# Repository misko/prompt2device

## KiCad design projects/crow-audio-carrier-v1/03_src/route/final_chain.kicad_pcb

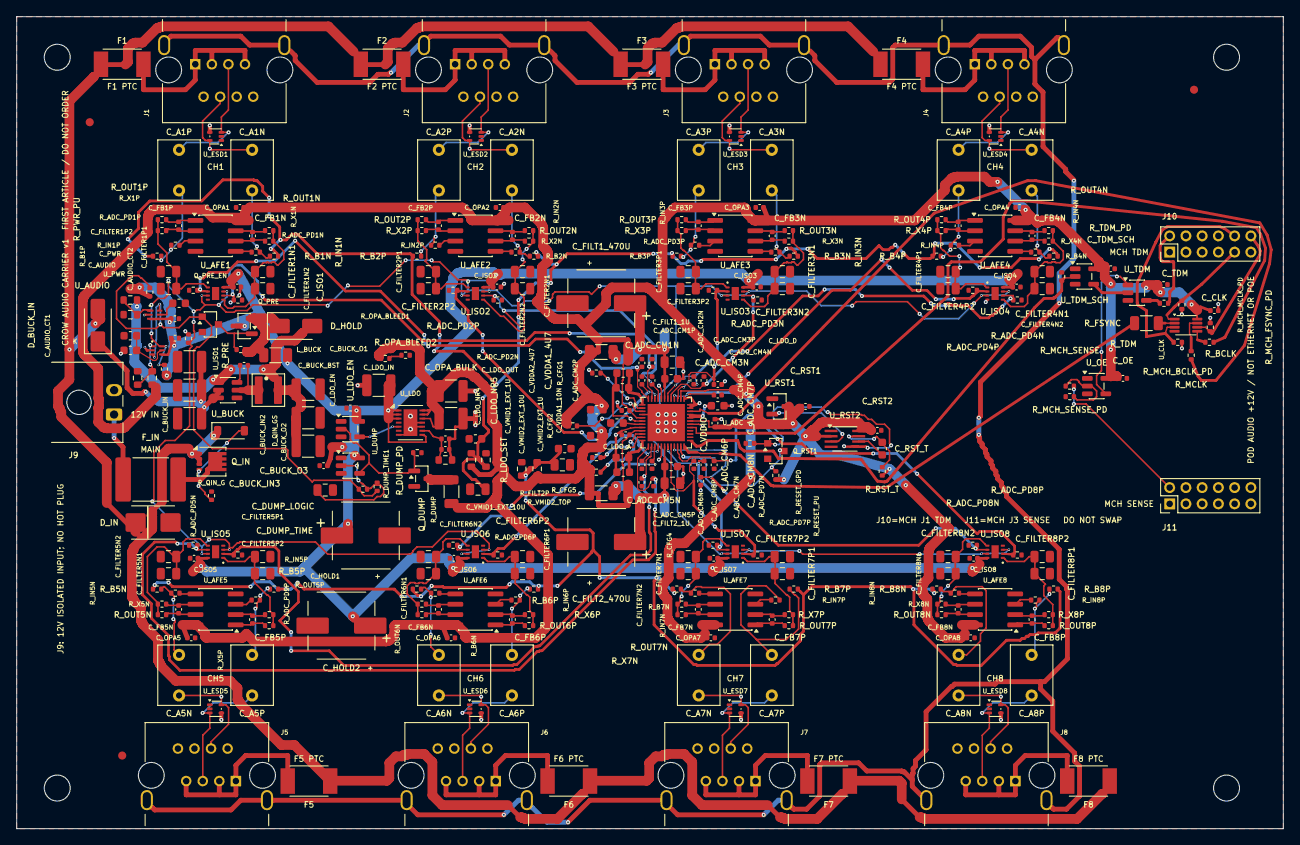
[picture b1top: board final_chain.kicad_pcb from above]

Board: 4 copper layers, 156.0 x 100.0 mm, 340 parts (0 on the bottom side), 179 nets.

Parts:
C_A1N, C_A1P, C_A2N, C_A2P, C_A3N, C_A3P, C_A4N, C_A4P, C_A5N, C_A5P, C_A6N, C_A6P, C_A7N, C_A7P, C_A8N, C_A8P: 1uF; C_Rect_L7.2mm_W5.0mm_P5.00mm
C_ADC_CM1N, C_ADC_CM1P, C_ADC_CM2N, C_ADC_CM2P, C_ADC_CM3N, C_ADC_CM3P, C_ADC_CM4N, C_ADC_CM4P, C_ADC_CM5N, C_ADC_CM5P, C_ADC_CM6N, C_ADC_CM6P, C_ADC_CM7N, C_ADC_CM7P, C_ADC_CM8N, C_ADC_CM8P: 1nF; C_0402_1005Metric
C_AUDIO: 100nF; C_0402_1005Metric
C_AUDIO_CT1, C_AUDIO_CT2: 1uF; C_0603_1608Metric
C_BUCK_BST: 100nF; C_0402_1005Metric
C_BUCK_IN, C_BUCK_IN2, C_BUCK_IN3: 10uF; C_1210_3225Metric
C_BUCK_O1, C_BUCK_O2, C_BUCK_O3: 47uF; C_1210_3225Metric
C_CLK: 100nF; C_0402_1005Metric
C_DUMP_LOGIC: 100nF; C_0402_1005Metric
C_DUMP_TIME: 15nF; C_0805_2012Metric
C_FB1N, C_FB1P, C_FB2N, C_FB2P, C_FB3N, C_FB3P, C_FB4N, C_FB4P, C_FB5N, C_FB5P, C_FB6N, C_FB6P, C_FB7N, C_FB7P, C_FB8N, C_FB8P: 680pF; C_0402_1005Metric
C_FILT1_1U, C_FILT2_1U: 1uF; C_0603_1608Metric
C_FILT1_10U, C_FILT2_10U: 10uF; C_0805_2012Metric
C_FILT1_470U, C_FILT2_470U: 470uF; Panasonic_EEEFK1A471P_8x10.2_Exact
C_FILTER1N1, C_FILTER1N2, C_FILTER1P1, C_FILTER1P2, C_FILTER2N1, C_FILTER2N2, C_FILTER2P1, C_FILTER2P2, C_FILTER3N1, C_FILTER3N2, C_FILTER3P1, C_FILTER3P2, C_FILTER4N1, C_FILTER4N2, C_FILTER4P1, C_FILTER4P2, C_FILTER5N1, C_FILTER5N2, C_FILTER5P1, C_FILTER5P2, C_FILTER6N1, C_FILTER6N2, C_FILTER6P1, C_FILTER6P2, C_FILTER7N1, C_FILTER7N2, C_FILTER7P1, C_FILTER7P2, C_FILTER8N1, C_FILTER8N2, C_FILTER8P1, C_FILTER8P2: 15nF; C_0805_2012Metric
C_HOLD1, C_HOLD2: 470uF; Panasonic_EEEFK1A471P_8x10.2_Exact
C_ISO1, C_ISO2, C_ISO3, C_ISO4, C_ISO5, C_ISO6, C_ISO7, C_ISO8: 100nF; C_0402_1005Metric
C_LDO_A: 4.7uF; C_0603_1608Metric
C_LDO_D: 4.7uF; C_0603_1608Metric
C_LDO_EN: 100nF; C_0402_1005Metric
C_LDO_IN: 47uF; C_1210_3225Metric
C_LDO_NR4, C_LDO_NR5: 1nF; C_0402_1005Metric
C_LDO_OUT: 47uF; C_1210_3225Metric
C_OE: 100nF; C_0402_1005Metric
C_OPA1, C_OPA2, C_OPA3, C_OPA4, C_OPA5, C_OPA6, C_OPA7, C_OPA8: 100nF; C_0402_1005Metric
C_OPA_BULK: 47uF; C_1210_3225Metric
C_PWR: 100nF; C_0402_1005Metric
C_PWR_CT: 1uF; C_0603_1608Metric
C_RST1, C_RST2: 100nF; C_0402_1005Metric
C_RST_T: 220nF; C_0603_1608Metric
C_TDM: 100nF; C_0402_1005Metric
C_TDM_SCH: 100nF; C_0402_1005Metric
C_VDDA1_4U7, C_VDDA2_4U7: 4.7uF; C_0603_1608Metric
C_VDDA1_10N, C_VDDA2_10N: 10nF; C_0402_1005Metric
C_VDDIO: 100nF; C_0402_1005Metric
C_VMID1_4U7, C_VMID2_4U7: 4.7uF; C_0603_1608Metric
C_VMID1_470N, C_VMID2_470N: 470nF; C_0603_1608Metric
C_VMID1_EXT_1U, C_VMID2_EXT_1U: 1uF; C_0603_1608Metric
C_VMID1_EXT_10U, C_VMID2_EXT_10U: 10uF; C_0805_2012Metric
D_BUCK_IN: US1B-13-F; D_SMA
D_HOLD: B340A-13-F; D_SMA
D_IN: SMBJ15A; Littelfuse_SMBJ15A_SMB_Exact
D_QIN_GS: BZT52C12-7-F; D_SOD-123
F1, F2, F3, F4, F5, F6, F7, F8: 1812L035/60MR; Littelfuse_1812L035_60_Exact
FID1, FID2, FID3: Fiducial_1mm_Mask2mm
F_IN: 2920L260/33DR; Fuse_2920_7451Metric
H1, H2, H3, H4: MountingHole_3.2mm_M3
J1, J2, J3, J4, J5, J6, J7, J8: 615008160221; Wurth_615008160221_RJ45
J9: 43650-0200; Molex_43650-0200_RA_Exact
J10, J11: TMM-106-01-L-D; Samtec_TMM-106-01-L-D_2x06_P2.00mm_Vertical
L_BUCK: XGL4020-332MEC; Coilcraft_XGL4020_Exact
Q_DUMP: AO3400A; SOT-23
Q_IN: DMP6023LFG-13; Diodes_PowerDI3333-8
Q_PRE: AO3401A; SOT-23
Q_PRE_EN: 2N7002K-7; Diodes_2N7002K_SOT23_Exact
Q_RST1: 2N7002K-7; Diodes_2N7002K_SOT23_Exact
R_ADC_BOT: 10kΩ; R_0603_1608Metric
R_ADC_PD1N, R_ADC_PD1P, R_ADC_PD2N, R_ADC_PD2P, R_ADC_PD3N, R_ADC_PD3P, R_ADC_PD4N, R_ADC_PD4P, R_ADC_PD5N, R_ADC_PD5P, R_ADC_PD6N, R_ADC_PD6P, R_ADC_PD7N, R_ADC_PD7P, R_ADC_PD8N, R_ADC_PD8P: 10kΩ; R_0402_1005Metric
R_ADC_TOP: 17.4kΩ; R_0603_1608Metric
R_AUDIO_PD: 100kΩ; R_0402_1005Metric
R_AUDIO_PU: 10kΩ; R_0402_1005Metric
R_B1N, R_B1P, R_B2N, R_B2P, R_B3N, R_B3P, R_B4N, R_B4P, R_B5N, R_B5P, R_B6N, R_B6P, R_B7N, R_B7P, R_B8N, R_B8P: 100kΩ; R_0402_1005Metric
R_BCLK: 22Ω; R_0402_1005Metric
R_CFG1, R_CFG4: 4.7kΩ; R_0402_1005Metric
R_CFG2: 0Ω; R_0402_1005Metric
R_CFG5: 100kΩ; R_0402_1005Metric
R_DUMP: 1Ω; R_1206_3216Metric
R_DUMP_PD: 100kΩ; R_0402_1005Metric
R_DUMP_TIME1, R_DUMP_TIME2: 100kΩ; R_0402_1005Metric
R_FILT1P, R_FILT2P: 1Ω; R_1206_3216Metric
R_FSYNC: 22Ω; R_1206_3216Metric
R_IN1N, R_IN1P, R_IN2N, R_IN2P, R_IN3N, R_IN3P, R_IN4N, R_IN4P, R_IN5N, R_IN5P, R_IN6N, R_IN6P, R_IN7N, R_IN7P, R_IN8N, R_IN8P: 10kΩ; R_0402_1005Metric
R_LDO_SET: 33kΩ; R_0603_1608Metric
R_MCH_BCLK_PD: 10kΩ; R_0402_1005Metric
R_MCH_FSYNC_PD: 10kΩ; R_0402_1005Metric
R_MCH_MCLK_PD: 10kΩ; R_0402_1005Metric
R_MCH_SENSE: 300Ω; R_0402_1005Metric
R_MCH_SENSE_PD: 10kΩ; R_0402_1005Metric
R_MCLK: 22Ω; R_0402_1005Metric
R_OPA_BLEED1, R_OPA_BLEED2: 100Ω; R_0402_1005Metric
R_OUT1N, R_OUT1P, R_OUT2N, R_OUT2P, R_OUT3N, R_OUT3P, R_OUT4N, R_OUT4P, R_OUT5N, R_OUT5P, R_OUT6N, R_OUT6P, R_OUT7N, R_OUT7P, R_OUT8N, R_OUT8P: 10Ω; R_0402_1005Metric
R_PRE: 22Ω; R_1206_3216Metric
R_PRE_G: 100kΩ; R_0402_1005Metric
R_PWR_BOT: 10kΩ; R_0603_1608Metric
R_PWR_PU: 10kΩ; R_0402_1005Metric
R_PWR_TOP: 30.9kΩ; Yageo_RT0603_NominalBody
R_QIN_G: 100kΩ; R_0402_1005Metric
R_RESET_GPD: 100kΩ; R_0402_1005Metric
R_RESET_PU: 10kΩ; R_0402_1005Metric
R_RST_T: 100kΩ; R_0402_1005Metric
R_TDM: 33Ω; R_0402_1005Metric
R_TDM_PD: 10kΩ; R_0402_1005Metric
R_VMID1_BOT, R_VMID1_TOP, R_VMID2_BOT, R_VMID2_TOP: 1kΩ; R_0603_1608Metric
R_X1N, R_X1P, R_X2N, R_X2P, R_X3N, R_X3P, R_X4N, R_X4P, R_X5N, R_X5P, R_X6N, R_X6P, R_X7N, R_X7P, R_X8N, R_X8P: 300Ω; R_0402_1005Metric
U_ADC: CS5308P-DN; Cirrus_CS5308P_QFN48_6x6_P0.4_EP4.6
U_AFE1, U_AFE2, U_AFE3, U_AFE4, U_AFE5, U_AFE6, U_AFE7, U_AFE8: OPA2320AIDR; SOIC-8_3.9x4.9mm_P1.27mm
U_AUDIO: TPS389001DSER; TI_DSE0006A_GNDToe018
U_BUCK: AP63205WU-7; TSOT-23-6
U_CLK: SN74LVC3G34DCUR; VSSOP-8_2.3x2mm_P0.5mm
U_DUMP: 74LVC1G14GV,125; SOT-23-5
U_ESD1, U_ESD2, U_ESD3, U_ESD4, U_ESD5, U_ESD6, U_ESD7, U_ESD8: TPD2E2U06DRLR; SOT-553
U_ISO1, U_ISO2, U_ISO3, U_ISO4, U_ISO5, U_ISO6, U_ISO7, U_ISO8: TMUX2821DSGR; TI_DSG0008A_Exact
U_LDO: LT3041ADE#TRPBF; DFN-14-1EP_3x4mm_P0.5mm_EP1.7x3.3mm
U_LDO_EN: 74LVC1G14GV,125; SOT-23-5
U_OE: 74LVC1G14GV,125; SOT-23-5
U_PWR: TPS389001DSER; TI_DSE0006A_GNDToe018
U_RST1: TPS3839K33DBZR; SOT-23
U_RST2: SN74LVC1G123DCTR; SSOP-8_2.95x2.8mm_P0.65mm
U_TDM: SN74LVC1G125DBVR; SOT-23-5
U_TDM_SCH: 74LVC1G17GV,125; SOT-23-5

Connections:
3V3_ADC: C_CLK.1, C_LDO_OUT.1, C_OE.1, C_OPA1.1, C_OPA2.1, C_OPA3.1, C_OPA4.1, C_OPA5.1, C_OPA6.1, C_OPA7.1, C_OPA8.1, C_OPA_BULK.1, C_RST1.1, C_RST2.1, C_TDM.1, C_TDM_SCH.1, C_VDDA1_4U7.1, C_VDDA1_10N.1, C_VDDA2_4U7.1, C_VDDA2_10N.1, C_VDDIO.1, R_ADC_TOP.1, R_CFG2.2, R_CFG4.2, R_DUMP.1, R_FILT1P.1, R_FILT2P.1, R_OPA_BLEED1.1, R_RESET_PU.1, R_RST_T.1, R_VMID1_TOP.1, R_VMID2_TOP.1, U_ADC.5, U_ADC.9, U_ADC.31, U_ADC.38, U_AFE1.8, U_AFE2.8, U_AFE3.8, U_AFE4.8, U_AFE5.8, U_AFE6.8, U_AFE7.8, U_AFE8.8, U_CLK.8, U_LDO.12, U_LDO.13, U_LDO.14, U_OE.5, U_RST1.3, U_RST2.2, U_RST2.8, U_TDM.5, U_TDM_SCH.5
5V_BUCK: C_BUCK_O1.1, C_BUCK_O2.1, C_BUCK_O3.1, D_HOLD.2, L_BUCK.2, R_PWR_TOP.1, U_BUCK.1
5V_LDO_FEED: D_HOLD.1, Q_PRE.2, R_PRE.1, R_PRE_G.2
5V_LDO_HOLD: C_AUDIO.1, C_DUMP_LOGIC.1, C_HOLD1.1, C_HOLD2.1, C_ISO1.1, C_ISO2.1, C_ISO3.1, C_ISO4.1, C_ISO5.1, C_ISO6.1, C_ISO7.1, C_ISO8.1, C_LDO_EN.1, C_LDO_IN.1, C_PWR.1, Q_PRE.3, R_AUDIO_PU.1, R_PRE.2, R_PWR_PU.1, U_AUDIO.4, U_DUMP.5, U_ISO1.8, U_ISO2.8, U_ISO3.8, U_ISO4.8, U_ISO5.8, U_ISO6.8, U_ISO7.8, U_ISO8.8, U_LDO.1, U_LDO.2, U_LDO.3, U_LDO.8, U_LDO_EN.5, U_PWR.3, U_PWR.4
12V_BUCK_IN: C_BUCK_IN.1, C_BUCK_IN2.1, C_BUCK_IN3.1, D_BUCK_IN.1, U_BUCK.2, U_BUCK.3
12V_FUSED: F_IN.2, Q_IN.5
12V_IN: F_IN.1, J9.1
12V_POD1: F1.2, J1.1, J1.3, J1.7
12V_POD2: F2.2, J2.1, J2.3, J2.7
12V_POD3: F3.2, J3.1, J3.3, J3.7
12V_POD4: F4.2, J4.1, J4.3, J4.7
12V_POD5: F5.2, J5.1, J5.3, J5.7
12V_POD6: F6.2, J6.1, J6.3, J6.7
12V_POD7: F7.2, J7.1, J7.3, J7.7
12V_POD8: F8.2, J8.1, J8.3, J8.7
12V_PROTECTED: D_BUCK_IN.2, D_IN.1, D_QIN_GS.1, F1.1, F2.1, F3.1, F4.1, F5.1, F6.1, F7.1, F8.1, Q_IN.1, Q_IN.2, Q_IN.3
ADC1N: C_ADC_CM1N.1, R_ADC_PD1N.1, U_ADC.47, U_ISO1.6
ADC1P: C_ADC_CM1P.1, R_ADC_PD1P.1, U_ADC.48, U_ISO1.2
ADC2N: C_ADC_CM2N.1, R_ADC_PD2N.1, U_ADC.45, U_ISO2.6
ADC2P: C_ADC_CM2P.1, R_ADC_PD2P.1, U_ADC.46, U_ISO2.2
ADC3N: C_ADC_CM3N.1, R_ADC_PD3N.1, U_ADC.41, U_ISO3.6
ADC3P: C_ADC_CM3P.1, R_ADC_PD3P.1, U_ADC.42, U_ISO3.2
ADC4N: C_ADC_CM4N.1, R_ADC_PD4N.1, U_ADC.39, U_ISO4.6
ADC4P: C_ADC_CM4P.1, R_ADC_PD4P.1, U_ADC.40, U_ISO4.2
ADC5N: C_ADC_CM5N.1, R_ADC_PD5N.1, U_ADC.13, U_ISO5.6
ADC5P: C_ADC_CM5P.1, R_ADC_PD5P.1, U_ADC.14, U_ISO5.2
ADC6N: C_ADC_CM6N.1, R_ADC_PD6N.1, U_ADC.15, U_ISO6.6
ADC6P: C_ADC_CM6P.1, R_ADC_PD6P.1, U_ADC.16, U_ISO6.2
ADC7N: C_ADC_CM7N.1, R_ADC_PD7N.1, U_ADC.19, U_ISO7.6
ADC7P: C_ADC_CM7P.1, R_ADC_PD7P.1, U_ADC.20, U_ISO7.2
ADC8N: C_ADC_CM8N.1, R_ADC_PD8N.1, U_ADC.21, U_ISO8.6
ADC8P: C_ADC_CM8P.1, R_ADC_PD8P.1, U_ADC.22, U_ISO8.2
ADC_BCLK: R_BCLK.2, U_ADC.29
ADC_DUMP: Q_DUMP.3, R_DUMP.2
ADC_FSYNC: R_FSYNC.2, U_ADC.24
ADC_MCLK: R_MCLK.2, U_ADC.34
ADC_RESET_N: Q_RST1.3, R_RESET_PU.2, U_ADC.23
ADC_SENSE: R_ADC_BOT.1, R_ADC_TOP.2, U_AUDIO.1
ADC_TDM: J10.2, R_TDM.2
AIN_N1: R_IN1N.2, U_AFE1.5
AIN_N2: R_IN2N.2, U_AFE2.5
AIN_N3: R_IN3N.2, U_AFE3.5
AIN_N4: R_IN4N.2, U_AFE4.5
AIN_N5: R_IN5N.2, U_AFE5.5
AIN_N6: R_IN6N.2, U_AFE6.5
AIN_N7: R_IN7N.2, U_AFE7.5
AIN_N8: R_IN8N.2, U_AFE8.5
AIN_P1: R_IN1P.2, U_AFE1.3
AIN_P2: R_IN2P.2, U_AFE2.3
AIN_P3: R_IN3P.2, U_AFE3.3
AIN_P4: R_IN4P.2, U_AFE4.3
AIN_P5: R_IN5P.2, U_AFE5.3
AIN_P6: R_IN6P.2, U_AFE6.3
AIN_P7: R_IN7P.2, U_AFE7.3
AIN_P8: R_IN8P.2, U_AFE8.3
AUDIO_CT: C_AUDIO_CT1.1, C_AUDIO_CT2.1, U_AUDIO.5
AUDIO_EN: R_AUDIO_PD.1, R_AUDIO_PU.2, U_AUDIO.6, U_ISO1.3, U_ISO1.7, U_ISO2.3, U_ISO2.7, U_ISO3.3, U_ISO3.7, U_ISO4.3, U_ISO4.7, U_ISO5.3, U_ISO5.7, U_ISO6.3, U_ISO6.7, U_ISO7.3, U_ISO7.7, U_ISO8.3, U_ISO8.7
AUDIO_N1: C_A1N.1, J1.4, U_ESD1.5
AUDIO_N2: C_A2N.1, J2.4, U_ESD2.5
AUDIO_N3: C_A3N.1, J3.4, U_ESD3.5
AUDIO_N4: C_A4N.1, J4.4, U_ESD4.5
AUDIO_N5: C_A5N.1, J5.4, U_ESD5.5
AUDIO_N6: C_A6N.1, J6.4, U_ESD6.5
AUDIO_N7: C_A7N.1, J7.4, U_ESD7.5
AUDIO_N8: C_A8N.1, J8.4, U_ESD8.5
AUDIO_P1: C_A1P.1, J1.5, U_ESD1.3
AUDIO_P2: C_A2P.1, J2.5, U_ESD2.3
AUDIO_P3: C_A3P.1, J3.5, U_ESD3.3
AUDIO_P4: C_A4P.1, J4.5, U_ESD4.3
AUDIO_P5: C_A5P.1, J5.5, U_ESD5.3
AUDIO_P6: C_A6P.1, J6.5, U_ESD6.3
AUDIO_P7: C_A7P.1, J7.5, U_ESD7.3
AUDIO_P8: C_A8P.1, J8.5, U_ESD8.3
BCLK_BUF: R_BCLK.1, U_CLK.5
BIAS_N1: C_A1N.2, R_B1N.1, R_IN1N.1
BIAS_N2: C_A2N.2, R_B2N.1, R_IN2N.1
BIAS_N3: C_A3N.2, R_B3N.1, R_IN3N.1
BIAS_N4: C_A4N.2, R_B4N.1, R_IN4N.1
BIAS_N5: C_A5N.2, R_B5N.1, R_IN5N.1
BIAS_N6: C_A6N.2, R_B6N.1, R_IN6N.1
BIAS_N7: C_A7N.2, R_B7N.1, R_IN7N.1
BIAS_N8: C_A8N.2, R_B8N.1, R_IN8N.1
BIAS_P1: C_A1P.2, R_B1P.1, R_IN1P.1
BIAS_P2: C_A2P.2, R_B2P.1, R_IN2P.1
BIAS_P3: C_A3P.2, R_B3P.1, R_IN3P.1
BIAS_P4: C_A4P.2, R_B4P.1, R_IN4P.1
BIAS_P5: C_A5P.2, R_B5P.1, R_IN5P.1
BIAS_P6: C_A6P.2, R_B6P.1, R_IN6P.1
BIAS_P7: C_A7P.2, R_B7P.1, R_IN7P.1
BIAS_P8: C_A8P.2, R_B8P.1, R_IN8P.1
BUCK_BST: C_BUCK_BST.1, U_BUCK.6
BUCK_SW: C_BUCK_BST.2, L_BUCK.1, U_BUCK.5
CFG1: R_CFG1.1, U_ADC.2
CFG2: R_CFG2.1, U_ADC.3
CFG4: R_CFG4.1, U_ADC.10
CFG5: R_CFG5.1, U_ADC.11
CHASSIS: J1.9, J1.10, J2.9, J2.10, J3.9, J3.10, J4.9, J4.10, J5.9, J5.10, J6.9, J6.10, J7.9, J7.10, J8.9, J8.10
DUMP_GATE: Q_DUMP.1, R_DUMP_PD.1, U_DUMP.4, U_LDO_EN.2
DUMP_RC: C_DUMP_TIME.1, R_DUMP_TIME1.2, R_DUMP_TIME2.2, U_DUMP.2
FB_N1: C_FB1N.1, R_X1N.1, U_AFE1.6
FB_N2: C_FB2N.1, R_X2N.1, U_AFE2.6
FB_N3: C_FB3N.1, R_X3N.1, U_AFE3.6
FB_N4: C_FB4N.1, R_X4N.1, U_AFE4.6
FB_N5: C_FB5N.1, R_X5N.1, U_AFE5.6
FB_N6: C_FB6N.1, R_X6N.1, U_AFE6.6
FB_N7: C_FB7N.1, R_X7N.1, U_AFE7.6
FB_N8: C_FB8N.1, R_X8N.1, U_AFE8.6
FB_P1: C_FB1P.1, R_X1P.1, U_AFE1.2
FB_P2: C_FB2P.1, R_X2P.1, U_AFE2.2
FB_P3: C_FB3P.1, R_X3P.1, U_AFE3.2
FB_P4: C_FB4P.1, R_X4P.1, U_AFE4.2
FB_P5: C_FB5P.1, R_X5P.1, U_AFE5.2
FB_P6: C_FB6P.1, R_X6P.1, U_AFE6.2
FB_P7: C_FB7P.1, R_X7P.1, U_AFE7.2
FB_P8: C_FB8P.1, R_X8P.1, U_AFE8.2
FILT1P: C_FILT1_1U.1, C_FILT1_10U.1, C_FILT1_470U.1, R_FILT1P.2, U_ADC.43
FILT2P: C_FILT2_1U.1, C_FILT2_10U.1, C_FILT2_470U.1, R_FILT2P.2, U_ADC.18
FILTER1N: C_FILTER1N1.1, C_FILTER1N2.1, R_OUT1N.2, R_X1N.2, U_ISO1.5
FILTER1P: C_FILTER1P1.1, C_FILTER1P2.1, R_OUT1P.2, R_X1P.2, U_ISO1.1
FILTER2N: C_FILTER2N1.1, C_FILTER2N2.1, R_OUT2N.2, R_X2N.2, U_ISO2.5
FILTER2P: C_FILTER2P1.1, C_FILTER2P2.1, R_OUT2P.2, R_X2P.2, U_ISO2.1
FILTER3N: C_FILTER3N1.1, C_FILTER3N2.1, R_OUT3N.2, R_X3N.2, U_ISO3.5
FILTER3P: C_FILTER3P1.1, C_FILTER3P2.1, R_OUT3P.2, R_X3P.2, U_ISO3.1
FILTER4N: C_FILTER4N1.1, C_FILTER4N2.1, R_OUT4N.2, R_X4N.2, U_ISO4.5
FILTER4P: C_FILTER4P1.1, C_FILTER4P2.1, R_OUT4P.2, R_X4P.2, U_ISO4.1
FILTER5N: C_FILTER5N1.1, C_FILTER5N2.1, R_OUT5N.2, R_X5N.2, U_ISO5.5
FILTER5P: C_FILTER5P1.1, C_FILTER5P2.1, R_OUT5P.2, R_X5P.2, U_ISO5.1
FILTER6N: C_FILTER6N1.1, C_FILTER6N2.1, R_OUT6N.2, R_X6N.2, U_ISO6.5
FILTER6P: C_FILTER6P1.1, C_FILTER6P2.1, R_OUT6P.2, R_X6P.2, U_ISO6.1
FILTER7N: C_FILTER7N1.1, C_FILTER7N2.1, R_OUT7N.2, R_X7N.2, U_ISO7.5
FILTER7P: C_FILTER7P1.1, C_FILTER7P2.1, R_OUT7P.2, R_X7P.2, U_ISO7.1
FILTER8N: C_FILTER8N1.1, C_FILTER8N2.1, R_OUT8N.2, R_X8N.2, U_ISO8.5
FILTER8P: C_FILTER8P1.1, C_FILTER8P2.1, R_OUT8P.2, R_X8P.2, U_ISO8.1
FSYNC_BUF: R_FSYNC.1, U_CLK.2
GND: C_ADC_CM1N.2, C_ADC_CM1P.2, C_ADC_CM2N.2, C_ADC_CM2P.2, C_ADC_CM3N.2, C_ADC_CM3P.2, C_ADC_CM4N.2, C_ADC_CM4P.2, C_ADC_CM5N.2, C_ADC_CM5P.2, C_ADC_CM6N.2, C_ADC_CM6P.2, C_ADC_CM7N.2, C_ADC_CM7P.2, C_ADC_CM8N.2, C_ADC_CM8P.2, C_AUDIO.2, C_AUDIO_CT1.2, C_AUDIO_CT2.2, C_BUCK_IN.2, C_BUCK_IN2.2, C_BUCK_IN3.2, C_BUCK_O1.2, C_BUCK_O2.2, C_BUCK_O3.2, C_CLK.2, C_DUMP_LOGIC.2, C_DUMP_TIME.2, C_FILT1_1U.2, C_FILT1_10U.2, C_FILT1_470U.2, C_FILT2_1U.2, C_FILT2_10U.2, C_FILT2_470U.2, C_FILTER1N1.2, C_FILTER1N2.2, C_FILTER1P1.2, C_FILTER1P2.2, C_FILTER2N1.2, C_FILTER2N2.2, C_FILTER2P1.2, C_FILTER2P2.2, C_FILTER3N1.2, C_FILTER3N2.2, C_FILTER3P1.2, C_FILTER3P2.2, C_FILTER4N1.2, C_FILTER4N2.2, C_FILTER4P1.2, C_FILTER4P2.2, C_FILTER5N1.2, C_FILTER5N2.2, C_FILTER5P1.2, C_FILTER5P2.2, C_FILTER6N1.2, C_FILTER6N2.2, C_FILTER6P1.2, C_FILTER6P2.2, C_FILTER7N1.2, C_FILTER7N2.2, C_FILTER7P1.2, C_FILTER7P2.2, C_FILTER8N1.2, C_FILTER8N2.2, C_FILTER8P1.2, C_FILTER8P2.2, C_HOLD1.2, C_HOLD2.2, C_ISO1.2, C_ISO2.2, C_ISO3.2, C_ISO4.2, C_ISO5.2, C_ISO6.2, C_ISO7.2, C_ISO8.2, C_LDO_A.2, C_LDO_D.2, C_LDO_EN.2, C_LDO_IN.2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
LDO_A_FILT: C_LDO_A.1, U_ADC.7
LDO_D_FILT: C_LDO_D.1, U_ADC.32, U_ADC.33
LDO_EN: U_LDO.5, U_LDO_EN.4
LDO_NR: C_LDO_NR4.1, C_LDO_NR5.1, R_LDO_SET.1, U_LDO.9
MCH_3V3_SENSE: J11.2, R_MCH_SENSE.1
MCH_BCLK: J10.10, R_MCH_BCLK_PD.1, U_CLK.3
MCH_FSYNC: J10.12, R_MCH_FSYNC_PD.1, U_CLK.6
MCH_MCLK: J10.9, R_MCH_MCLK_PD.1, U_CLK.1
MCLK_BUF: R_MCLK.1, U_CLK.7
OPA_BLEED_A: R_OPA_BLEED1.2, R_OPA_BLEED2.1
OPA_N1: C_FB1N.2, R_OUT1N.1, U_AFE1.7
OPA_N2: C_FB2N.2, R_OUT2N.1, U_AFE2.7
OPA_N3: C_FB3N.2, R_OUT3N.1, U_AFE3.7
OPA_N4: C_FB4N.2, R_OUT4N.1, U_AFE4.7
OPA_N5: C_FB5N.2, R_OUT5N.1, U_AFE5.7
OPA_N6: C_FB6N.2, R_OUT6N.1, U_AFE6.7
OPA_N7: C_FB7N.2, R_OUT7N.1, U_AFE7.7
OPA_N8: C_FB8N.2, R_OUT8N.1, U_AFE8.7
OPA_P1: C_FB1P.2, R_OUT1P.1, U_AFE1.1
OPA_P2: C_FB2P.2, R_OUT2P.1, U_AFE2.1
OPA_P3: C_FB3P.2, R_OUT3P.1, U_AFE3.1
OPA_P4: C_FB4P.2, R_OUT4P.1, U_AFE4.1
OPA_P5: C_FB5P.2, R_OUT5P.1, U_AFE5.1
OPA_P6: C_FB6P.2, R_OUT6P.1, U_AFE6.1
OPA_P7: C_FB7P.2, R_OUT7P.1, U_AFE7.1
OPA_P8: C_FB8P.2, R_OUT8P.1, U_AFE8.1
POR_N: U_RST1.2, U_RST2.3
PRE_GATE: Q_PRE.1, Q_PRE_EN.3, R_PRE_G.1
PWR_CT: C_PWR_CT.1, U_PWR.5
PWR_EN: Q_PRE_EN.1, R_DUMP_TIME1.1, R_DUMP_TIME2.1, R_PWR_PU.2, U_AUDIO.3, U_PWR.6
PWR_SENSE: R_PWR_BOT.1, R_PWR_TOP.2, U_PWR.1
Q_IN_GATE: D_QIN_GS.2, Q_IN.4, R_QIN_G.1
RESET_C: C_RST_T.1, U_RST2.6
RESET_PULSE_H: Q_RST1.1, R_RESET_GPD.1, U_RST2.5
RESET_RC: C_RST_T.2, R_RST_T.2, U_RST2.7
TDM_BUFFERED: R_TDM.1, U_TDM.4
TDM_CLEAN: U_TDM.2, U_TDM_SCH.4
TDM_OE_N: U_OE.4, U_TDM.1
TDM_RAW: R_TDM_PD.1, U_ADC.25, U_TDM_SCH.2
TDM_SENSE_G: R_MCH_SENSE.2, R_MCH_SENSE_PD.1, U_OE.2
VMID1: C_VMID1_4U7.1, C_VMID1_470N.1, U_ADC.1
VMID1_EXT: C_VMID1_EXT_1U.1, C_VMID1_EXT_10U.1, R_B1N.2, R_B1P.2, R_B2N.2, R_B2P.2, R_B3N.2, R_B3P.2, R_B4N.2, R_B4P.2, R_VMID1_BOT.1, R_VMID1_TOP.2
VMID2: C_VMID2_4U7.1, C_VMID2_470N.1, U_ADC.12
VMID2_EXT: C_VMID2_EXT_1U.1, C_VMID2_EXT_10U.1, R_B5N.2, R_B5P.2, R_B6N.2, R_B6P.2, R_B7N.2, R_B7P.2, R_B8N.2, R_B8P.2, R_VMID2_BOT.1, R_VMID2_TOP.2

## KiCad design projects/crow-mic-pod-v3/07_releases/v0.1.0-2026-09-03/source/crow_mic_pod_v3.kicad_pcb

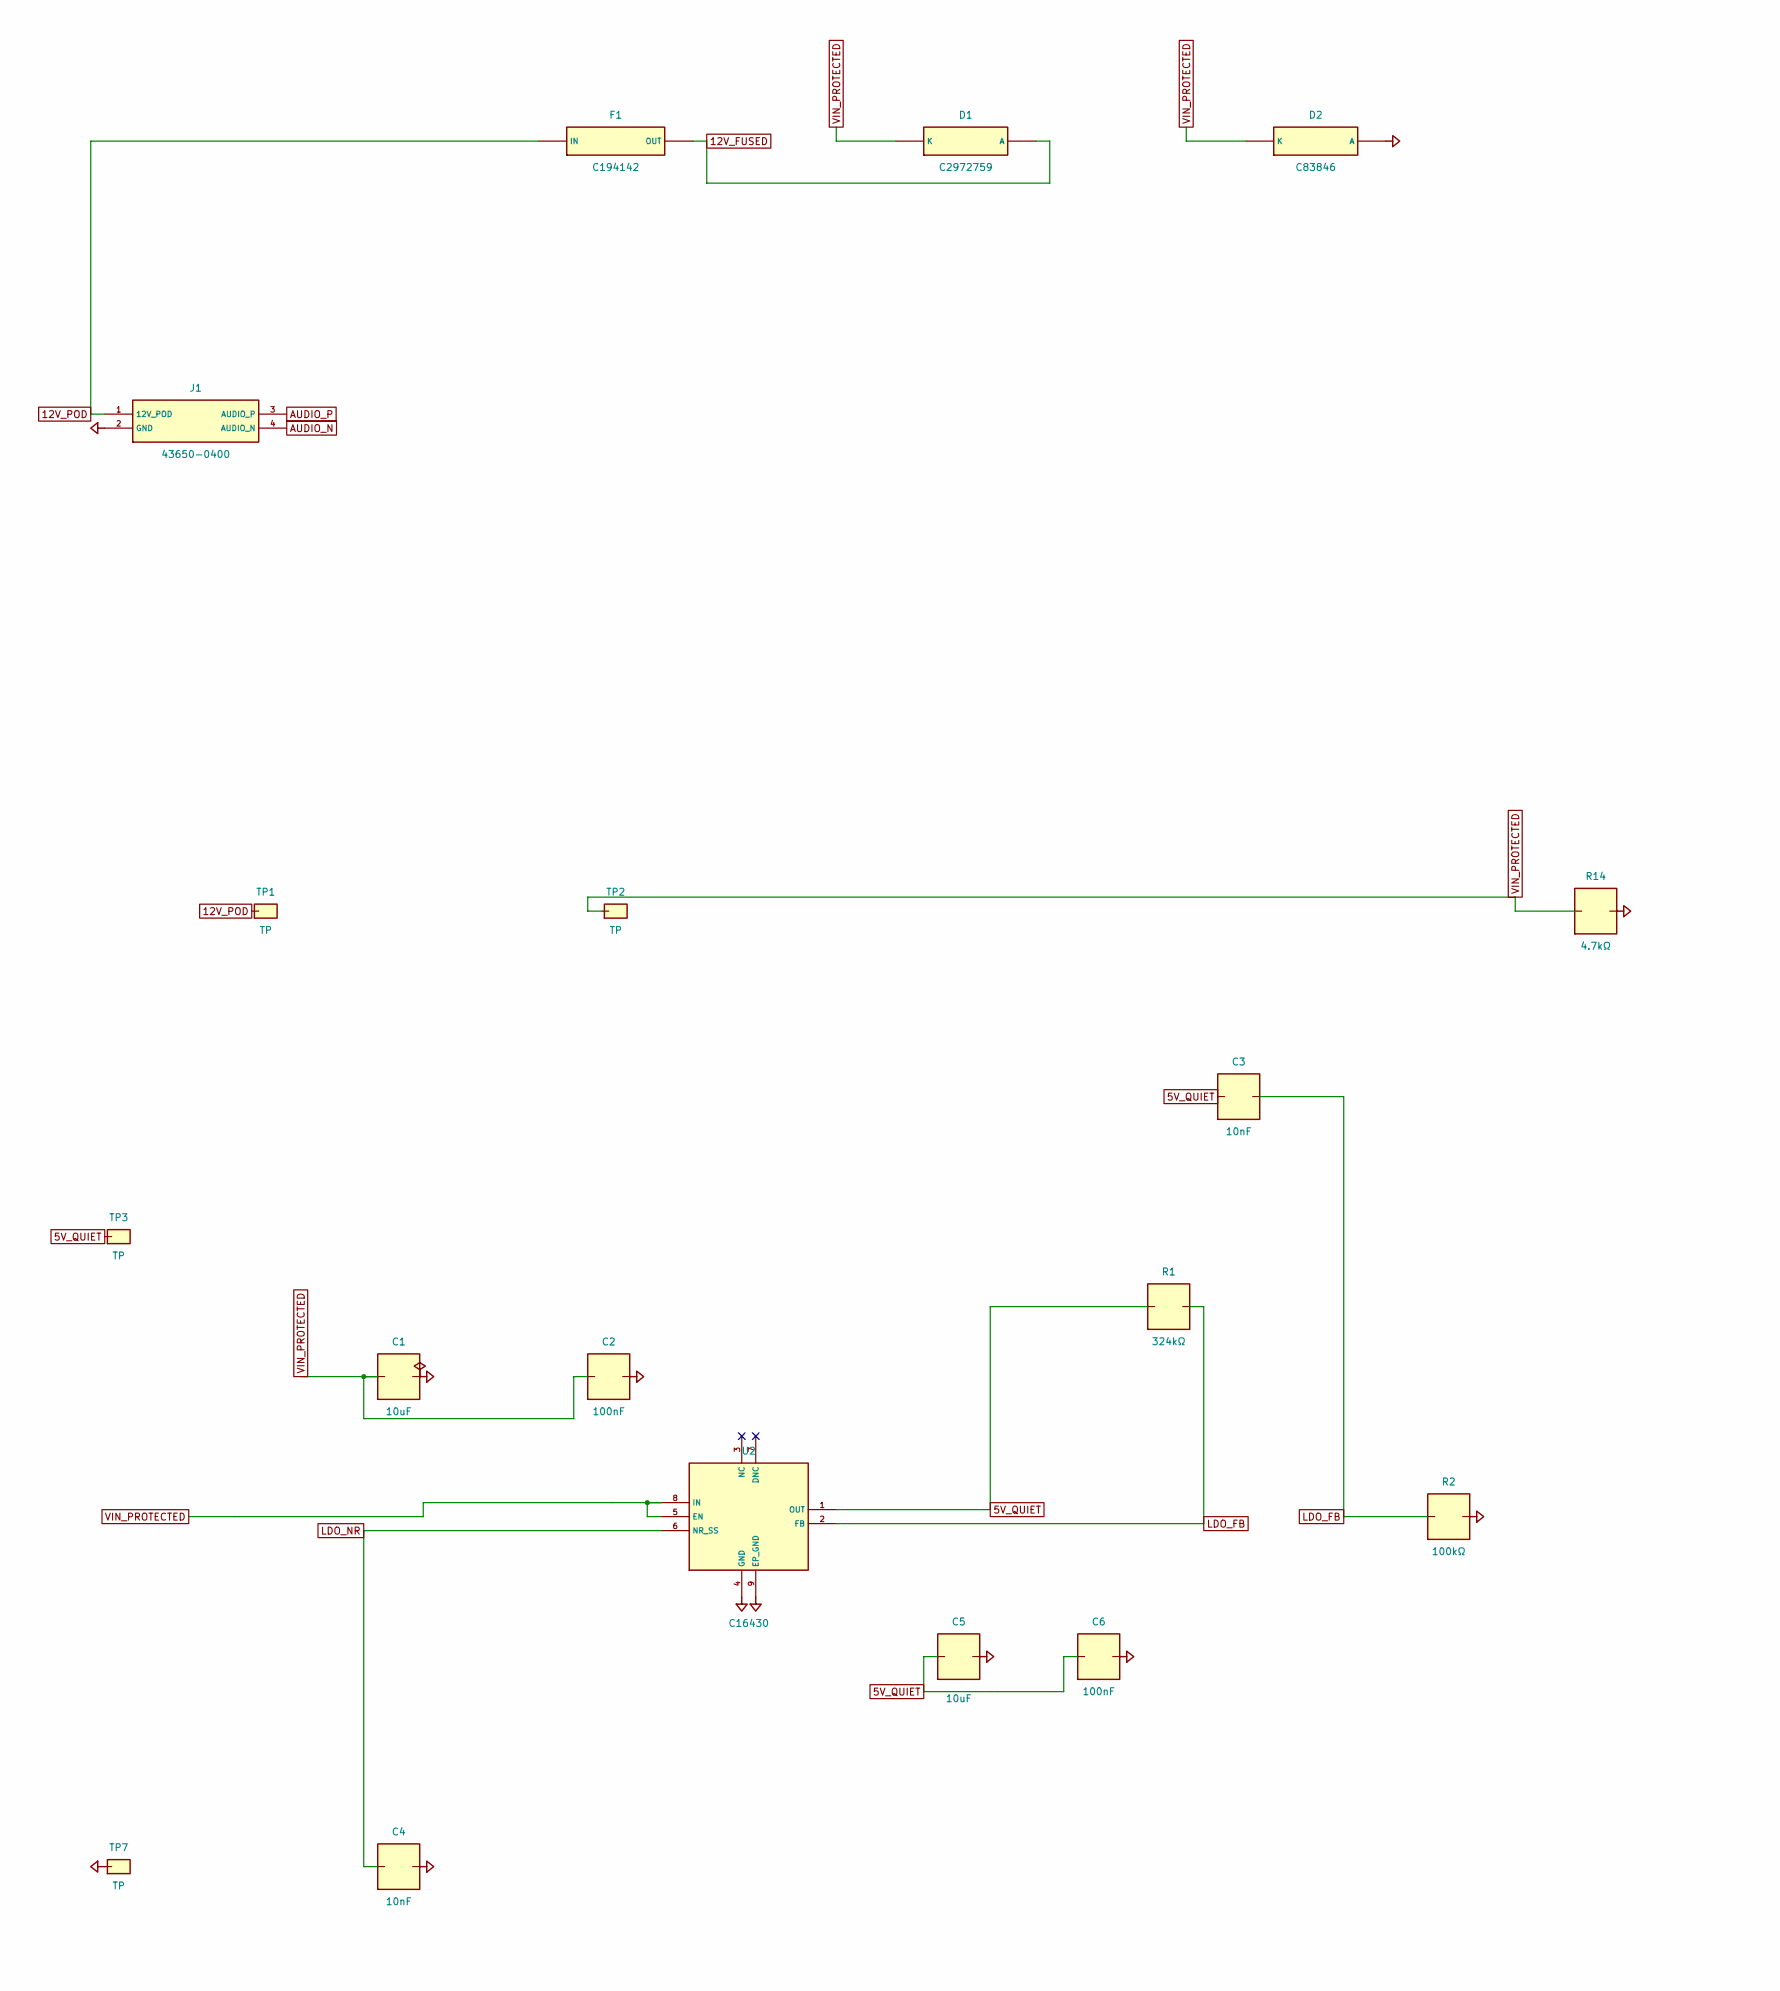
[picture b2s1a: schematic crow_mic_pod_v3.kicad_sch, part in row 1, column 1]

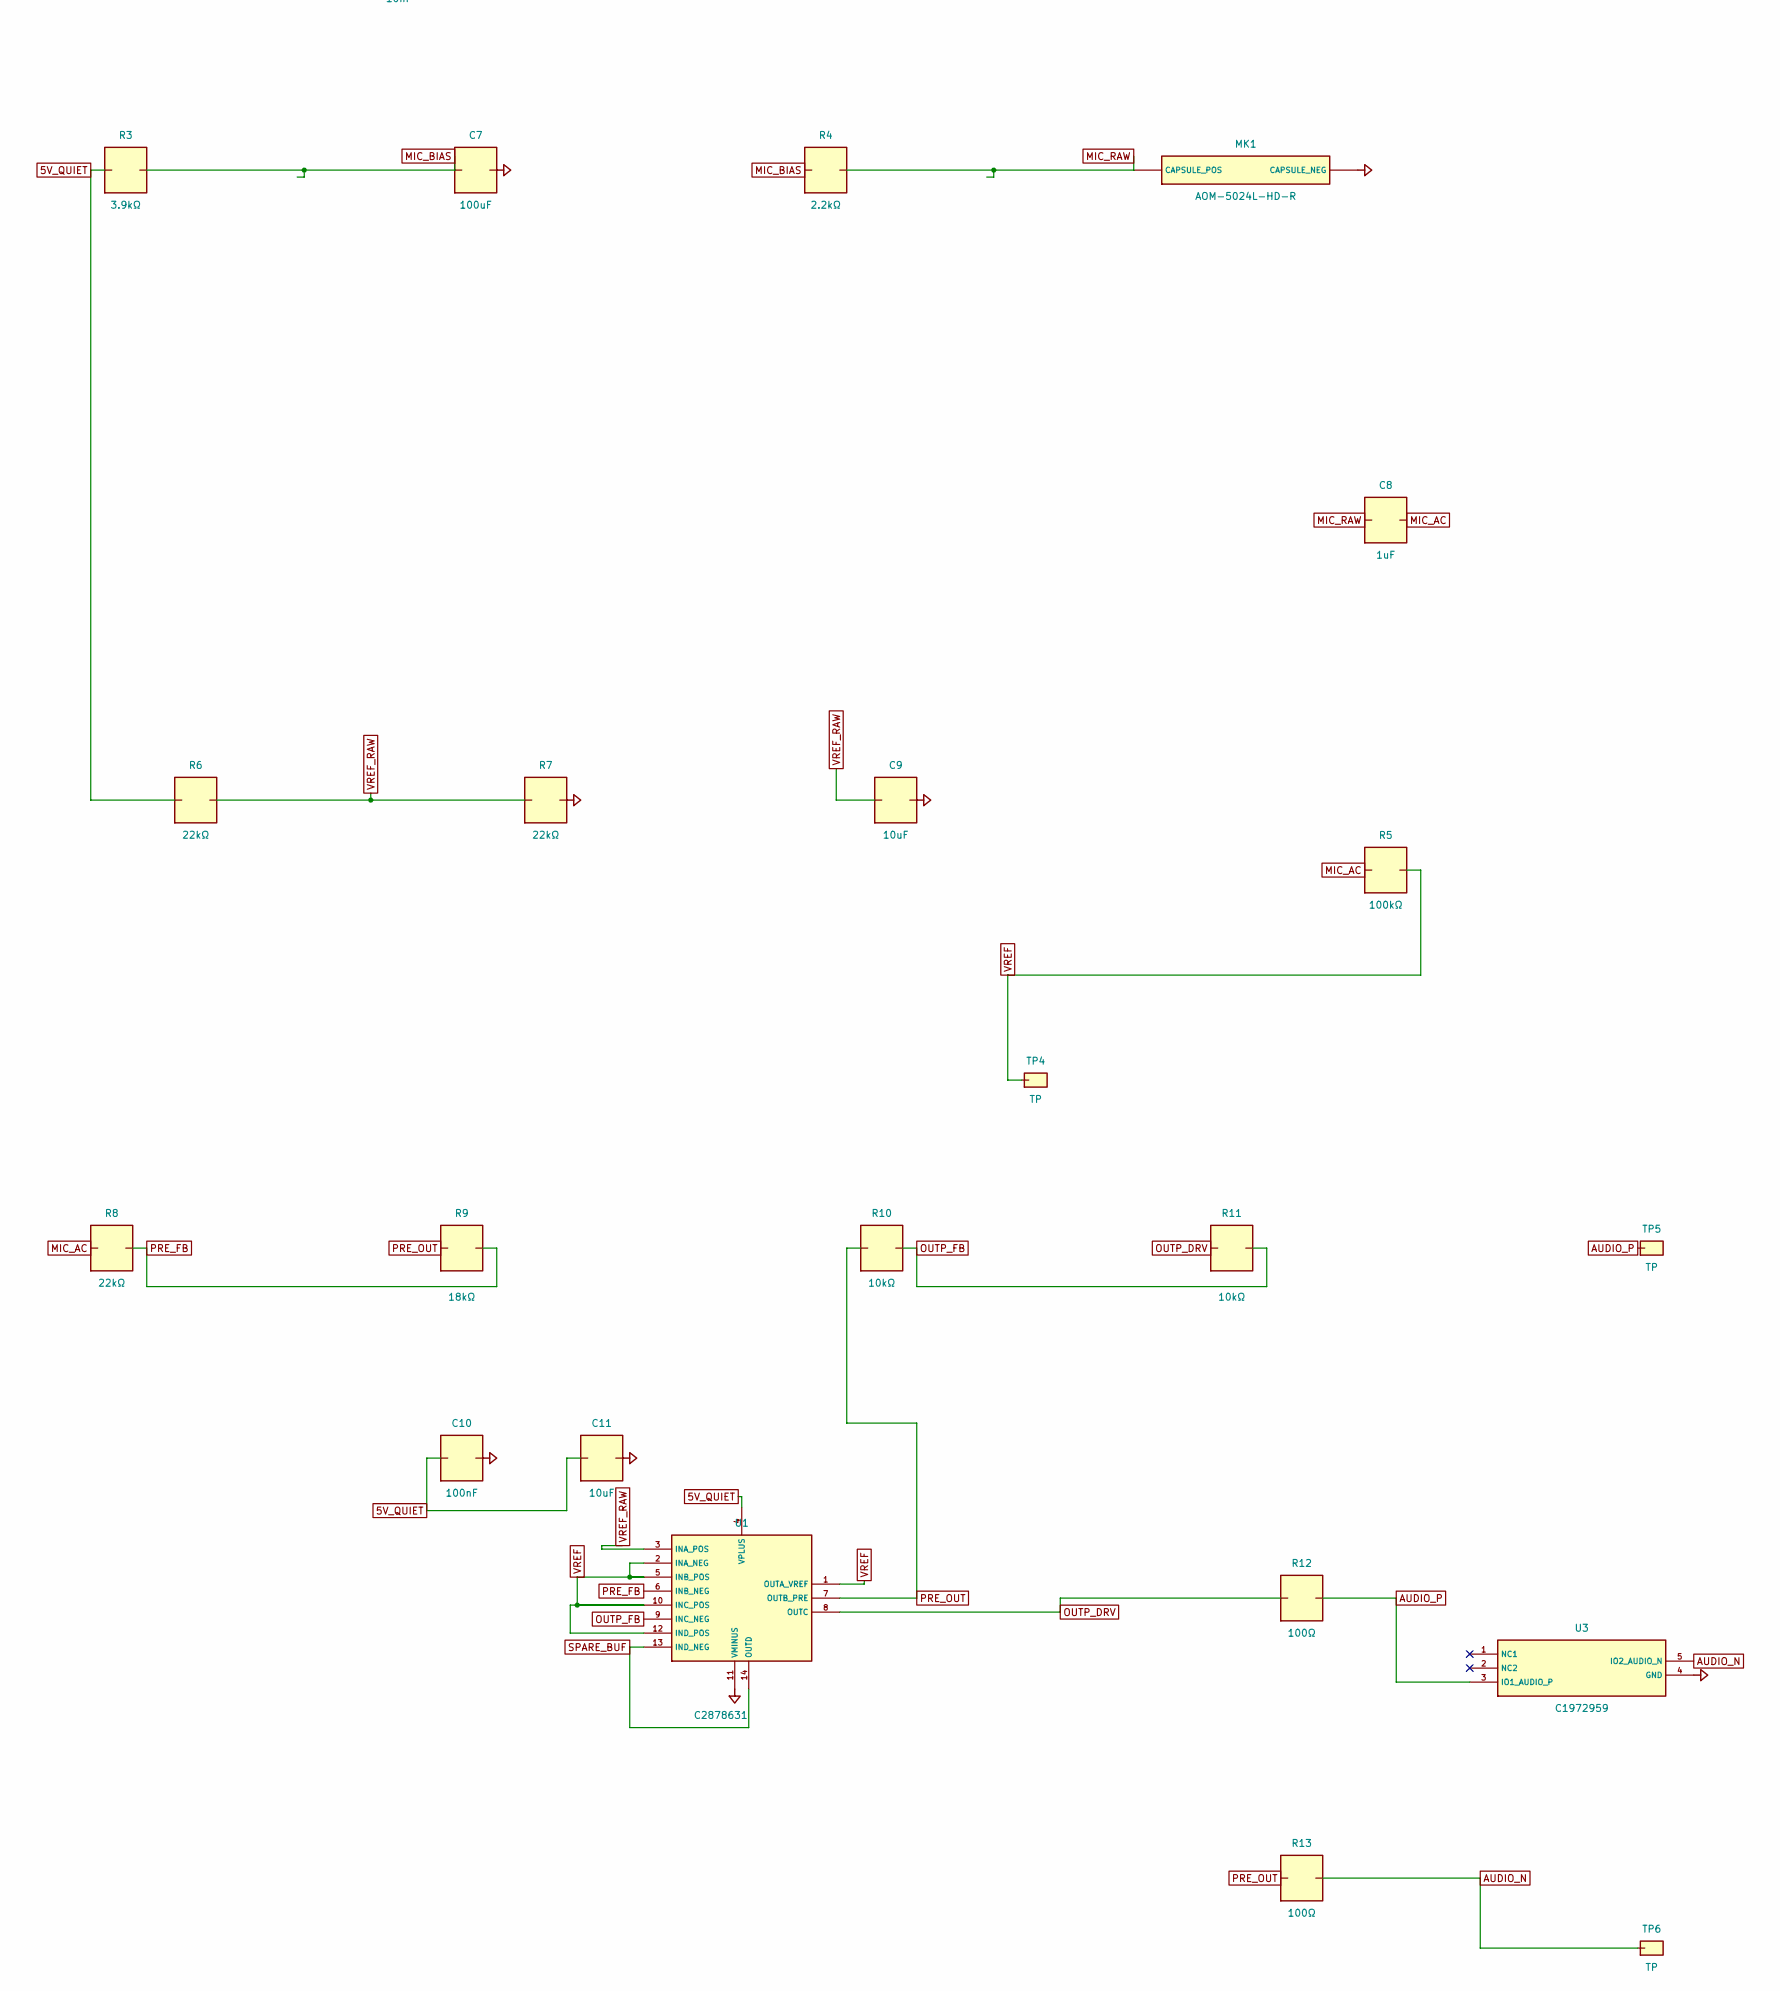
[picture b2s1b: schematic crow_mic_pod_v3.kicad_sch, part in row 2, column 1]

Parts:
C1: 10uF; C_1210_3225Metric
C2, C6, C10: 100nF; C_0402_1005Metric
C3, C4: 10nF; C_0402_1005Metric
C5, C9, C11: 10uF; C_0805_2012Metric
C7: 100uF; C_1210_3225Metric
C8: 1uF; C_0603_1608Metric
D1: C2972759; JKSEMI_1N4007_M7_SMA
D2: C83846; Littelfuse_SMBJ15A_SMB
F1: C194142; Fuse_1206_3216Metric
J1: 43650-0400; Molex_Micro-Fit_3.0_43650-0400_1x04_P3.00mm_Horizontal
MK1: AOM-5024L-HD-R; Mic_Wire_Pads_P5.00mm
R1: 324kΩ; R_0402_1005Metric
R2, R5: 100kΩ; R_0402_1005Metric
R3: 3.9kΩ; R_0805_2012Metric
R4: 2.2kΩ; R_0402_1005Metric
R6, R7, R8: 22kΩ; R_0402_1005Metric
R9: 18kΩ; R_0402_1005Metric
R10, R11: 10kΩ; R_0402_1005Metric
R12, R13: 100Ω; R_0805_2012Metric
R14: 4.7kΩ; R_1206_3216Metric
TP1, TP2, TP3, TP4, TP5, TP6, TP7: TP; TestPoint_Pad_D1.5mm
U1: C2878631; TI_OPA1679_SOIC-14_D
U2: C16430; TI_TPS7A4901_DGN0008D
U3: C1972959; TI_TPD2E2U06_DRL

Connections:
5V_QUIET: C3.1, C5.1, C6.1, C10.1, C11.1, R1.1, R3.1, R6.1, TP3.1, U1.4 (VPLUS), U2.1 (OUT)
12V_FUSED: D1.2 (A), F1.2 (OUT)
12V_POD: F1.1 (IN), J1.1 (12V_POD), TP1.1
AUDIO_N: J1.4 (AUDIO_N), R13.2, TP6.1, U3.5 (IO2_AUDIO_N)
AUDIO_P: J1.3 (AUDIO_P), R12.2, TP5.1, U3.3 (IO1_AUDIO_P)
GND: C1.2, C2.2, C4.2, C5.2, C6.2, C7.2, C9.2, C10.2, C11.2, D2.2 (A), J1.2 (GND), MK1.2 (CAPSULE_NEG), R2.2, R7.2, R14.2, TP7.1, U1.11 (VMINUS), U2.4 (GND), U2.9 (EP_GND), U3.4 (GND)
LDO_FB: C3.2, R1.2, R2.1, U2.2 (FB)
LDO_NR: C4.1, U2.6 (NR_SS)
MIC_AC: C8.2, R5.1, R8.1
MIC_BIAS: C7.1, R3.2, R4.1
MIC_RAW: C8.1, MK1.1 (CAPSULE_POS), R4.2
OUTP_DRV: R11.1, R12.1, U1.8 (OUTC)
OUTP_FB: R10.2, R11.2, U1.9 (INC_NEG)
PRE_FB: R8.2, R9.2, U1.6 (INB_NEG)
PRE_OUT: R9.1, R10.1, R13.1, U1.7 (OUTB_PRE)
SPARE_BUF: U1.13 (IND_NEG), U1.14 (OUTD)
VIN_PROTECTED: C1.1, C2.1, D1.1 (K), D2.1 (K), R14.1, TP2.1, U2.5 (EN), U2.8 (IN)
VREF: R5.2, TP4.1, U1.1 (OUTA_VREF), U1.2 (INA_NEG), U1.5 (INB_POS), U1.10 (INC_POS), U1.12 (IND_POS)
VREF_RAW: C9.1, R6.2, R7.1, U1.3 (INA_POS)

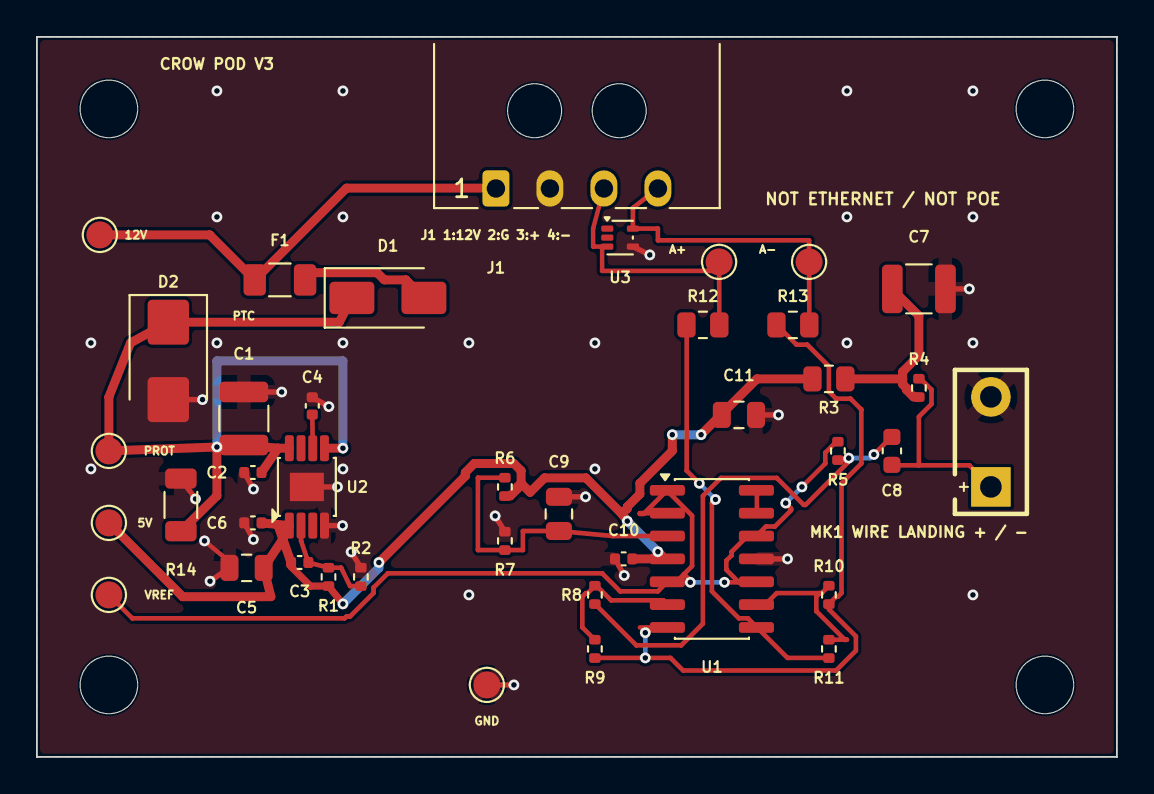
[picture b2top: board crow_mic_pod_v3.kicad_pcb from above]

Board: 2 copper layers, 60.0 x 40.0 mm, 44 parts (0 on the bottom side), 19 nets.

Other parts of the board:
H1, H2, H3, H4: MountingHole_3.2mm_M3

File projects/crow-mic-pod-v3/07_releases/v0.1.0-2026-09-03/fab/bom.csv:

Comment,Designator,Footprint,MPN,LCSC
0ZCJ0010FF2E,F1,Fuse_1206_3216Metric,0ZCJ0010FF2E,C194142
100kΩ,"R2,R5",R_0402_1005Metric,0402WGF1003TCE,C25741
100nF,C2,C_0402_1005Metric,CC0402KRX7R9BB104,C131394
100nF,"C10,C6",C_0402_1005Metric,CL05B104KO5NNNC,C1525
100uF,C7,C_1210_3225Metric,GRM32ER61A107ME20L,C84455
100Ω,"R12,R13",R_0805_2012Metric,0805W8F1000T5E,C17408
10kΩ,"R10,R11",R_0402_1005Metric,RC0402FR-0710KL,C60490
10nF,"C3,C4",C_0402_1005Metric,CL05B103KB5NNNC,C15195
10uF,"C11,C5,C9",C_0805_2012Metric,CL21A106KAYNNNE,C15850
10uF,C1,C_1210_3225Metric,GRM32ER71H106KA12L,C77102
18kΩ,R9,R_0402_1005Metric,0402WGF1802TCE,C25762
1N4007(M7)SMA,D1,JKSEMI_1N4007_M7_SMA,1N4007(M7)SMA,C2972759
1uF,C8,C_0603_1608Metric,CL10A105KB8NNNC,C15849
2.2kΩ,R4,R_0402_1005Metric,0402WGF2201TCE,C25879
22kΩ,"R6,R7,R8",R_0402_1005Metric,0402WGF2202TCE,C25768
3.9kΩ,R3,R_0805_2012Metric,0805W8F3901T5E,C17614
324kΩ,R1,R_0402_1005Metric,0402WGF3243TCE,C113480
4.7kΩ,R14,R_1206_3216Metric,1206W4F4701T5E,C17936
OPA1679IDR,U1,TI_OPA1679_SOIC-14_D,OPA1679IDR,C2878631
SMBJ15A,D2,Littelfuse_SMBJ15A_SMB,SMBJ15A,C83846
TPD2E2U06DRLR,U3,TI_TPD2E2U06_DRL,TPD2E2U06DRLR,C1972959
TPS7A4901DGNR,U2,TI_TPS7A4901_DGN0008D,TPS7A4901DGNR,C16430

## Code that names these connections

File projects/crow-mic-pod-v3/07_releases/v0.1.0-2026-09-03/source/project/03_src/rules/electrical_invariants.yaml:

invariants:
  - {assert: pin_on_net, pin: "J1.1", net: 12V_POD, adr: "0001", why: "Frozen spoke pin 1 is pod power."}
  - {assert: pin_on_net, pin: "J1.2", net: GND, adr: "0001", why: "Frozen spoke pin 2 is the power/audio return."}
  - {assert: pin_on_net, pin: "J1.3", net: AUDIO_P, adr: "0001", why: "Frozen spoke pin 3 is the positive audio leg."}
  - {assert: pin_on_net, pin: "J1.4", net: AUDIO_N, adr: "0001", why: "Frozen spoke pin 4 is the negative audio leg."}
  - assert: series_chain
    chain: [12V_POD, F1, 12V_FUSED, D1, VIN_PROTECTED]
    adr: "0002"
    why: "The local PTC and low-leakage forward rectifier precede every pod load."
  - {assert: pin_on_net, pin: "D1.1", net: VIN_PROTECTED, adr: "0002", why: "1N4007 cathode faces the protected node."}
  - {assert: pin_on_net, pin: "D1.2", net: 12V_FUSED, adr: "0002", why: "1N4007 anode receives correctly polarized fused input."}
  - {assert: pin_on_net, pin: "D2.1", net: VIN_PROTECTED, adr: "0002", why: "SMBJ15A cathode clamps the protected positive rail."}
  - {assert: pin_on_net, pin: "U2.8", net: VIN_PROTECTED, adr: "0002", why: "TPS7A4901 input is protected."}
  - {assert: pin_on_net, pin: "U2.5", net: VIN_PROTECTED, adr: "0002", why: "TPS7A4901 enable is always on only after protection."}
  - {assert: pin_on_net, pin: "U2.1", net: 5V_QUIET, adr: "0002", why: "TPS7A4901 output owns the quiet rail."}
  - {assert: pin_on_net, pin: "U2.9", net: GND, adr: "0002", why: "TPS7A4901 exposed pad is grounded."}
  - {assert: net_has_part, net: VIN_PROTECTED, part_type: capacitor, min: 2, adr: "0002", why: "Protected input has local bulk and HF bypass."}
  - {assert: part_value, part: R14, equals: 4.7k, tolerance_pct: 1, adr: "0002", why: "The hot D1 reverse-leakage bound times R14 remains inside the TPS7A49 negative absolute limit."}
  - {assert: part_value, part: R1, equals: 324k, tolerance_pct: 1, adr: "0002", why: "LDO upper feedback resistor sets the governed rail window."}
  - {assert: part_value, part: R2, equals: 100k, tolerance_pct: 1, adr: "0002", why: "LDO lower feedback resistor sets the governed rail window."}
  - {assert: part_value, part: R3, equals: 3.9k, tolerance_pct: 1, adr: "0002", why: "Bias filter derives the characterized nominal 3 V microphone supply plane from 5V_QUIET."}
  - {assert: part_value, part: C7, equals: 100u, tolerance_pct: 20, adr: "0002", why: "Bias reservoir and R3 replace the archived 100 ohm/100 uF low-frequency rejection weakness."}
  - {assert: part_value, part: R4, equals: 2.2k, tolerance_pct: 1, adr: "0002", why: "Capsule loading matches the PUI sensitivity characterization circuit."}
  - {assert: part_value, part: R8, equals: 22k, tolerance_pct: 1, adr: "0003", why: "Preamp input resistance is the denominator of the 9/11 inverting magnitude gain."}
  - {assert: part_value, part: R9, equals: 18k, tolerance_pct: 1, adr: "0003", why: "Preamp feedback resistance fixes the 9/11 magnitude and the 18/11 differential gain."}
  - {assert: part_value, part: R10, equals: 10k, tolerance_pct: 1, adr: "0003", why: "Positive-leg polarity restore uses equal resistors."}
  - {assert: part_value, part: R11, equals: 10k, tolerance_pct: 1, adr: "0003", why: "Positive-leg polarity restore uses equal resistors."}
  - {assert: part_value, part: R12, equals: 100, tolerance_pct: 1, adr: "0003", why: "AUDIO_P source impedance is exactly governed."}
  - {assert: part_value, part: R13, equals: 100, tolerance_pct: 1, adr: "0003", why: "AUDIO_N source impedance is exactly governed."}
  - {assert: pin_on_net, pin: "U1.7", net: PRE_OUT, adr: "0003", why: "OPA1679 B channel produces the inverting preamp output."}
  - {assert: pin_on_net, pin: "U1.8", net: OUTP_DRV, adr: "0003", why: "OPA1679 C channel restores positive acoustic polarity."}
  - {assert: pin_on_net, pin: "R13.1", net: PRE_OUT, adr: "0003", why: "The already low-impedance U1B output drives the complementary leg without a second signal buffer."}
  - {assert: pin_on_net, pin: "U1.12", net: VREF, adr: "0003", why: "The spare D channel sees only the fixed in-range reference voltage."}
  - {assert: pin_on_net, pin: "U1.13", net: SPARE_BUF, adr: "0003", why: "The spare D channel closes local unity feedback on a private net."}
  - {assert: pin_on_net, pin: "U1.14", net: SPARE_BUF, adr: "0003", why: "The spare D output is parked as a private VREF follower and never parallels another output."}
  - {assert: pin_on_net, pin: "U3.3", net: AUDIO_P, adr: "0003", why: "ESD channel one clamps only AUDIO_P."}
  - {assert: pin_on_net, pin: "U3.5", net: AUDIO_N, adr: "0003", why: "ESD channel two clamps only AUDIO_N."}
